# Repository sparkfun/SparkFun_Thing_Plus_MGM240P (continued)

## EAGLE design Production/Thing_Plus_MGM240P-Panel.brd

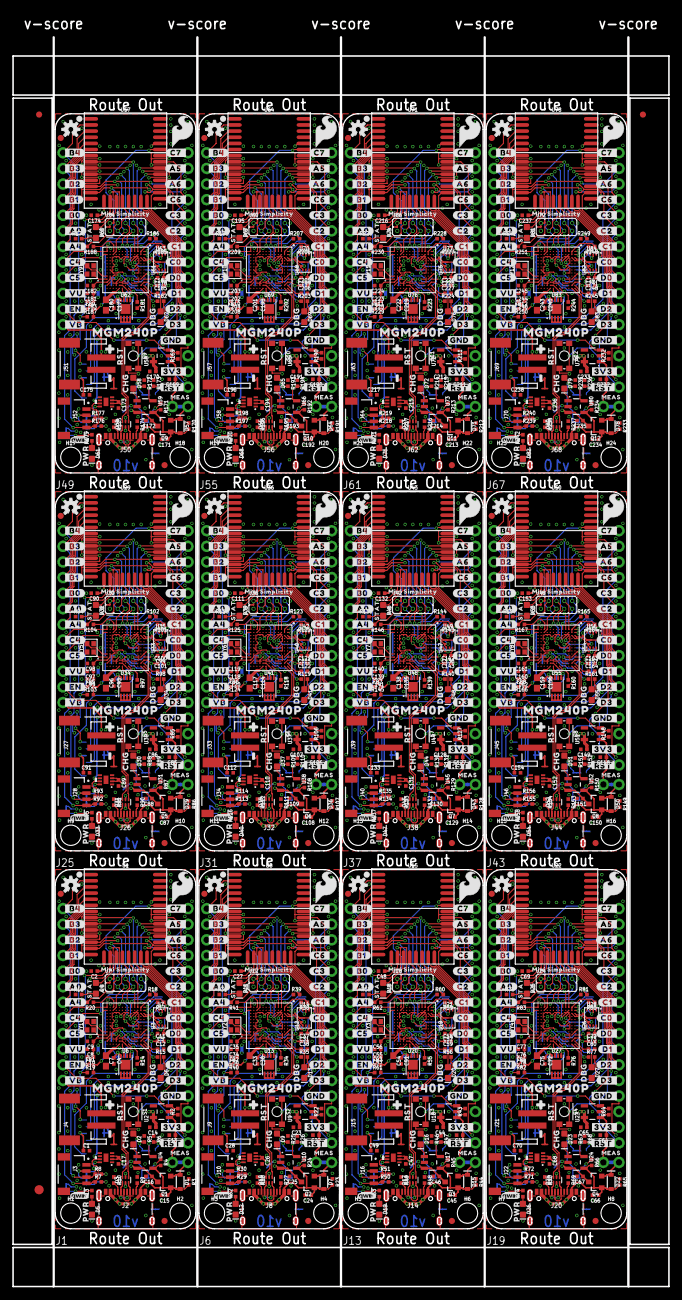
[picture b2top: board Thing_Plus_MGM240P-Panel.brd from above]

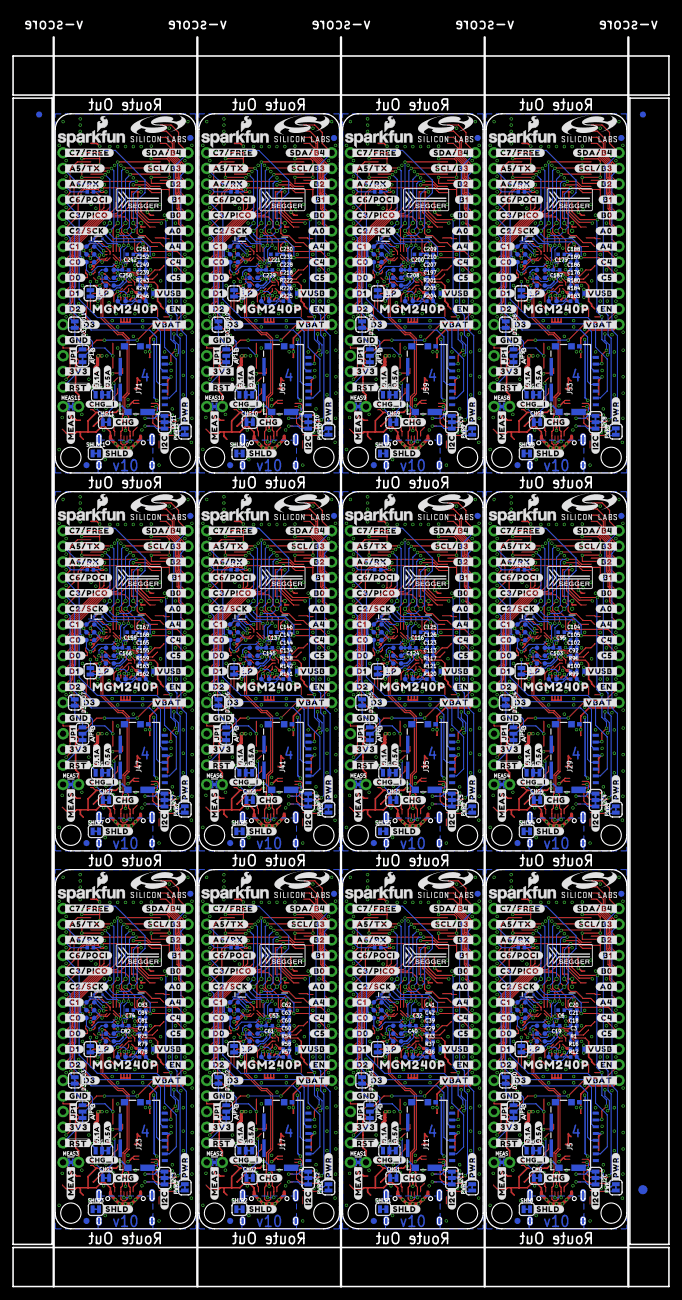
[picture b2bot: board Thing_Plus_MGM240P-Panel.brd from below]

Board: 4 copper layers, 106.7 x 203.2 mm, 2178 parts (963 on the bottom side), 948 nets.

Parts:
C1, C6, C28, C32, C49, C53, C70, C74, C91, C95, C112, C116, C133, C137, C154, C158, C175, C179, C196, C200, C217, C221, C238, C242: 10uF; 0402-TIGHT
C2, C3, C4, C5, C17, C18, C19, C20, C21, C26, C27, C29, C30, C31, C39, C40, C41, C42, C47, C48, C50, C51, C52, C60, C61, C62, C63, C68, C69, C71, C72, C73, C81, C82, C83, C84, C89, C90, C92, C93, C94, C102, C103, C104, C105, C110, C111, C113, C114, C115, C123, C124, C125, C126, C131, C132, C134, C135, C136, C144, C145, C146, C147, C152, C153, C155, C156, C157, C165, C166, C167, C168, C173, C174, C176, C177, C178, C186, C187, C188, C189, C194, C195, C197, C198, C199, C207, C208, C209, C210, C215, C216, C218, C219, C220, C228, C229, C230, C231, C236, C237, C239, C240, C241, C249, C250, C251, C252: 0.1uF; 0402-TIGHT
C7, C33, C54, C75, C96, C117, C138, C159, C180, C201, C222, C243: 1.0uF; 0603
C8, C9, C34, C35, C55, C56, C76, C77, C97, C98, C118, C119, C139, C140, C160, C161, C181, C182, C202, C203, C223, C224, C244, C245: 10nF; 0402-TIGHT
C10, C11, C13, C22, C36, C37, C43, C57, C58, C64, C78, C79, C85, C99, C100, C106, C120, C121, C127, C141, C142, C148, C162, C163, C169, C183, C184, C190, C204, C205, C211, C225, C226, C232, C246, C247: 1.0uF; 0402-TIGHT
C12, C15, C16, C24, C25, C38, C45, C46, C59, C66, C67, C80, C87, C88, C101, C108, C109, C122, C129, C130, C143, C150, C151, C164, C171, C172, C185, C192, C193, C206, C213, C214, C227, C234, C235, C248: 4.7uF; 0402-TIGHT
C14, C23, C44, C65, C86, C107, C128, C149, C170, C191, C212, C233: 2.2uF; 0402-TIGHT
CHG, CHG1, CHG2, CHG3, CHG4, CHG5, CHG6, CHG7, CHG8, CHG9, CHG10, CHG11: JUMPER-SMT_2_NC_TRACE_SILK; SMT-JUMPER_2_NC_TRACE_SILK
CHG_I, CHG_I1, CHG_I2, CHG_I3, CHG_I4, CHG_I5, CHG_I6, CHG_I7, CHG_I8, CHG_I9, CHG_I10, CHG_I11: JUMPER-SMT_3_1-NC_TRACE_SILK; SMT-JUMPER_3_1-NC_TRACE_SILK
D1, D7, D15, D22, D29, D36, D43, D50, D57, D64, D71, D78: 1A/23V/620mV; SOD-323
D2, D9, D16, D23, D30, D37, D44, D51, D58, D65, D72, D79: Yellow; LED-0603
D3, D10, D17, D24, D31, D38, D45, D52, D59, D66, D73, D80: PRTR5V0U2F; SOT886
D3_ISO, D3_ISO1, D3_ISO2, D3_ISO3, D3_ISO4, D3_ISO5, D3_ISO6, D3_ISO7, D3_ISO8, D3_ISO9, D3_ISO10, D3_ISO11: JUMPER-SMT_2_NC_TRACE_SILK; SMT-JUMPER_2_NC_TRACE_SILK
D4, D6, D11, D13, D18, D20, D25, D27, D32, D34, D39, D41, D46, D48, D53, D55, D60, D62, D67, D69, D74, D76, D81, D83: BLUE; LED-0603
D5, D12, D19, D26, D33, D40, D47, D54, D61, D68, D75, D82: RED; LED-0603
D8, D14, D21, D28, D35, D42, D49, D56, D63, D70, D77, D84: 120mA/40V/370mV; SOD-523
E$1, E$2, E$3, E$4: FIDUCIAL-1X2
E$5, E$6: FIDUCIAL-1.5X3
FB1, FB2, FB3, FB4, FB5, FB6, FB7, FB8, FB9, FB10, FB11, FB12: FERRITE_BEAD-120_OHM-0402T; 0402-TIGHT
FD1, FD2, FD3, FD4, FD5, FD6, FD7, FD8, FD9, FD10, FD11, FD12, FD13, FD14, FD15, FD16, FD17, FD18, FD19, FD20, FD21, FD22, FD23, FD24, FD25, FD26, FD27, FD28, FD29, FD30, FD31, FD32, FD33, FD34, FD35, FD36, FD37, FD38, FD39, FD40, FD41, FD42, FD43, FD44, FD45, FD46, FD47, FD48: FIDUCIAL1X2; FIDUCIAL-1X2
H1, H2, H3, H4, H5, H6, H7, H8, H9, H10, H11, H12, H13, H14, H15, H16, H17, H18, H19, H20, H21, H22, H23, H24: STAND-OFF
I2C, I2C1, I2C2, I2C3, I2C4, I2C5, I2C6, I2C7, I2C8, I2C9, I2C10, I2C11: JUMPER-SMT_3_2-NC_TRACE_SILK; SMT-JUMPER_3_2-NC_TRACE_SILK
J1, J6, J13, J19, J25, J31, J37, J43, J49, J55, J61, J67: THING_PLUS_LOGICAL; THING_PLUS
J2, J8, J14, J20, J26, J32, J38, J44, J50, J56, J62, J68: USB Female Type C Connector; USB-C-16P-4LAYER-ISOLATED
J3, J10, J16, J22, J28, J34, J40, J46, J52, J58, J64, J70: QWIIC_RIGHT_ANGLE; JST04_1MM_RA
J4, J9, J15, J21, J27, J33, J39, J45, J51, J57, J63, J69: JST-2-SMD
J5, J11, J17, J23, J29, J35, J41, J47, J53, J59, J65, J71: MICRO-SDFRICTION; MICROSD_TINY
J7, J12, J18, J24, J30, J36, J42, J48, J54, J60, J66, J72: 2X5_PTH_SILK_.05
JP1, JP2, JP3, JP4, JP5, JP6, JP7, JP8, JP9, JP10, JP11, JP12: JUMPER-SMT_3_1-NC_TRACE_SILK; SMT-JUMPER_3_1-NC_TRACE_SILK
LOGO1, LOGO4, LOGO7, LOGO10, LOGO13, LOGO16, LOGO19, LOGO22, LOGO25, LOGO28, LOGO31, LOGO34: SFE_LOGO_NAME_FLAME.1_INCH; SFE_LOGO_NAME_FLAME_.1
LOGO2, LOGO5, LOGO8, LOGO11, LOGO14, LOGO17, LOGO20, LOGO23, LOGO26, LOGO29, LOGO32, LOGO35: QWIIC_LOGO_3MM; QWIIC_3MM
LOGO3, LOGO6, LOGO9, LOGO12, LOGO15, LOGO18, LOGO21, LOGO24, LOGO27, LOGO30, LOGO33, LOGO36: OSHW-LOGOS; OSHW-LOGO-S
LP, LP1, LP2, LP3, LP4, LP5, LP6, LP7, LP8, LP9, LP10, LP11: JUMPER-SMT_2_NC_TRACE_SILK; SMT-JUMPER_2_NC_TRACE_SILK
MEAS, MEAS1, MEAS2, MEAS3, MEAS4, MEAS5, MEAS6, MEAS7, MEAS8, MEAS9, MEAS10, MEAS11: JUMPER-COMBO_2_NC_TRACE; COMBO-JUMPER_2_NC_TRACE
PWR, PWR1, PWR2, PWR3, PWR4, PWR5, PWR6, PWR7, PWR8, PWR9, PWR10, PWR11: JUMPER-SMT_2_NC_TRACE_SILK; SMT-JUMPER_2_NC_TRACE_SILK
Q1, Q2, Q3, Q4, Q5, Q6, Q7, Q8, Q9, Q10, Q11, Q12: 20V/4.2A/52mΩ/1.4W; SOT23-3
R1, R13, R18, R32, R33, R39, R53, R54, R60, R74, R75, R81, R95, R96, R102, R116, R117, R123, R137, R138, R144, R158, R159, R165, R179, R180, R186, R200, R201, R207, R221, R222, R228, R242, R243, R249: 1k; 0402-TIGHT
R2, R3, R6, R17, R22, R23, R26, R38, R43, R44, R47, R59, R64, R65, R68, R80, R85, R86, R89, R101, R106, R107, R110, R122, R127, R128, R131, R143, R148, R149, R152, R164, R169, R170, R173, R185, R190, R191, R194, R206, R211, R212, R215, R227, R232, R233, R236, R248: 10k; 0402-TIGHT
R4, R24, R45, R66, R87, R108, R129, R150, R171, R192, R213, R234: 4.7k; 0402-TIGHT
R5, R25, R46, R67, R88, R109, R130, R151, R172, R193, R214, R235: 2.0K; 0402-TIGHT
R7, R8, R11, R12, R15, R16, R29, R30, R31, R35, R36, R37, R50, R51, R52, R56, R57, R58, R71, R72, R73, R77, R78, R79, R92, R93, R94, R98, R99, R100, R113, R114, R115, R119, R120, R121, R134, R135, R136, R140, R141, R142, R155, R156, R157, R161, R162, R163, R176, R177, R178, R182, R183, R184, R197, R198, R199, R203, R204, R205, R218, R219, R220, R224, R225, R226, R239, R240, R241, R245, R246, R247: 2.2k; 0402-TIGHT
R9, R10, R27, R28, R48, R49, R69, R70, R90, R91, R111, R112, R132, R133, R153, R154, R174, R175, R195, R196, R216, R217, R237, R238: 5.1k; 0402-TIGHT
R14, R19, R34, R40, R55, R61, R76, R82, R97, R103, R118, R124, R139, R145, R160, R166, R181, R187, R202, R208, R223, R229, R244, R250: 100k; 0402-TIGHT
R20, R21, R41, R42, R62, R63, R83, R84, R104, R105, R125, R126, R146, R147, R167, R168, R188, R189, R209, R210, R230, R231, R251, R252: 330; 0402-TIGHT
S1, S2, S3, S4, S5, S6, S7, S8, S9, S10, S11, S12: MOMENTARY-SWITCH-SPST-SMD-4.6X2.8MM; TACTILE_SWITCH_SMD_4.6X2.8MM
SHLD, SHLD1, SHLD2, SHLD3, SHLD4, SHLD5, SHLD6, SHLD7, SHLD8, SHLD9, SHLD10, SHLD11: JUMPER-SMT_2_NC_TRACE_SILK; SMT-JUMPER_2_NC_TRACE_SILK
TP1, TP2, TP3, TP4, TP5, TP6, TP7, TP8, TP9, TP10, TP11, TP12, TP13, TP14, TP15, TP16, TP17, TP18, TP19, TP20, TP21, TP22, TP23, TP24, TP25, TP26, TP27, TP28, TP29, TP30, TP31, TP32, TP33, TP34, TP35, TP36, TP37, TP38, TP39, TP40, TP41, TP42, TP43, TP44, TP45, TP46, TP47, TP48, TP49, TP50, TP51, TP52, TP53, TP54, TP55, TP56, TP57, TP58, TP59, TP60, TP61, TP62, TP63, TP64, TP65, TP66, TP67, TP68, TP69, TP70, TP71, TP72, TP73, TP74, TP75, TP76, TP77, TP78, TP79, TP80, TP81, TP82, TP83, TP84, TP85, TP86, TP87, TP88, TP89, TP90, TP91, TP92, TP93, TP94, TP95, TP96, TP97, TP98, TP99, TP100, TP101, TP102, TP103, TP104, TP105, TP106, TP107, TP108, TP109, TP110, TP111, TP112, TP113, TP114, TP115, TP116, TP117, TP118, TP119, TP120, TP121, TP122, TP123, TP124, TP125, TP126, TP127, TP128, TP129, TP130, TP131, TP132, TP133, TP134, TP135, TP136, TP137, TP138, TP139, TP140, TP141, TP142, TP143, TP144, TP145, TP146, TP147, TP148, TP149, TP150, TP151, TP152, TP153, TP154, TP155, TP156, TP157, TP158, TP159, TP160, TP161, TP162, TP163, TP164, TP165, TP166, TP167, TP168: TEST-POINT3; PAD.03X.03
U1, U8, U15, U22, U29, U36, U43, U50, U57, U64, U71, U78: MGM240P
U2, U9, U16, U23, U30, U37, U44, U51, U58, U65, U72, U79: XC6222B331MR-G; SOT23-5
U3, U12, U19, U26, U33, U40, U47, U54, U61, U68, U75, U82: EFM32GG12B410F1024GL120
U4, U10, U17, U24, U31, U38, U45, U52, U59, U66, U73, U80: MCP73831; SOT23-5
U5, U11, U18, U25, U32, U39, U46, U53, U60, U67, U74, U81: MAX17048; DFN-8
U6, U13, U20, U27, U34, U41, U48, U55, U62, U69, U76, U83: M24C02-FMC6TG
U7, U14, U21, U28, U35, U42, U49, U56, U63, U70, U77, U84: MX25R8035FZUIL0
U$1, U$110, U$193, U$276, U$359, U$442, U$525, U$608, U$691, U$774, U$857, U$940: #_B4#0
U$2, U$111, U$194, U$277, U$360, U$443, U$526, U$609, U$692, U$775, U$858, U$941: #_B3#0
U$3, U$112, U$195, U$278, U$361, U$444, U$527, U$610, U$693, U$776, U$859, U$942: #_B2#0
U$4, U$113, U$196, U$279, U$362, U$445, U$528, U$611, U$694, U$777, U$860, U$943: #_B1#0
U$5, U$84, U$167, U$250, U$333, U$416, U$499, U$582, U$665, U$748, U$831, U$914: #SHLD#0
U$6, U$114, U$197, U$280, U$363, U$446, U$529, U$612, U$695, U$778, U$861, U$944: #_B0#0
U$7, U$115, U$198, U$281, U$364, U$447, U$530, U$613, U$696, U$779, U$862, U$945: #_A0#0
U$8, U$158, U$241, U$324, U$407, U$490, U$573, U$656, U$739, U$822, U$905, U$988: #_A4#0
U$9, U$116, U$199, U$282, U$365, U$448, U$531, U$614, U$697, U$780, U$863, U$946: #_C5#0
U$10, U$117, U$200, U$283, U$366, U$449, U$532, U$615, U$698, U$781, U$864, U$947: #_C4#0
U$11, U$118, U$201, U$284, U$367, U$450, U$533, U$616, U$699, U$782, U$865, U$948: #C7_#0
U$12, U$119, U$202, U$285, U$368, U$451, U$534, U$617, U$700, U$783, U$866, U$949: #A5_#0
U$13, U$120, U$203, U$286, U$369, U$452, U$535, U$618, U$701, U$784, U$867, U$950: #A6_#0
U$14, U$121, U$204, U$287, U$370, U$453, U$536, U$619, U$702, U$785, U$868, U$951: #C6_#0
U$15, U$122, U$205, U$288, U$371, U$454, U$537, U$620, U$703, U$786, U$869, U$952: #C3_#0
U$16, U$123, U$206, U$289, U$372, U$455, U$538, U$621, U$704, U$787, U$870, U$953: #C2_#0
U$17, U$124, U$207, U$290, U$373, U$456, U$539, U$622, U$705, U$788, U$871, U$954: #C1_#0
U$18, U$125, U$208, U$291, U$374, U$457, U$540, U$623, U$706, U$789, U$872, U$955: #C0_#0
U$19, U$105, U$188, U$271, U$354, U$437, U$520, U$603, U$686, U$769, U$852, U$935: #PWR#0
U$20, U$106, U$189, U$272, U$355, U$438, U$521, U$604, U$687, U$770, U$853, U$936: PWR0
U$21, U$85, U$168, U$251, U$334, U$417, U$500, U$583, U$666, U$749, U$832, U$915: #GND_#0
U$22, U$86, U$169, U$252, U$335, U$418, U$501, U$584, U$667, U$750, U$833, U$916: #3V3_#0
U$23, U$58, U$91, U$101, U$174, U$184, U$257, U$267, U$340, U$350, U$423, U$433, U$506, U$516, U$589, U$599, U$672, U$682, U$755, U$765, U$838, U$848, U$921, U$931: MGM240P0
U$24, U$126, U$209, U$292, U$375, U$458, U$541, U$624, U$707, U$790, U$873, U$956: #D0_#0
U$25, U$87, U$170, U$253, U$336, U$419, U$502, U$585, U$668, U$751, U$834, U$917: #_VB#0
U$26, U$88, U$171, U$254, U$337, U$420, U$503, U$586, U$669, U$752, U$835, U$918: #_VU#0
U$27, U$89, U$172, U$255, U$338, U$421, U$504, U$587, U$670, U$753, U$836, U$919: #_EN#0
U$28, U$90, U$173, U$256, U$339, U$422, U$505, U$588, U$671, U$754, U$837, U$920: ##RST##0
U$29, U$92, U$175, U$258, U$341, U$424, U$507, U$590, U$673, U$756, U$839, U$922: SFE_LOGO_FLAME_.2
U$30, U$93, U$176, U$259, U$342, U$425, U$508, U$591, U$674, U$757, U$840, U$923: #0
U$31, U$94, U$177, U$260, U$343, U$426, U$509, U$592, U$675, U$758, U$841, U$924: #1
U$32, U$127, U$210, U$293, U$376, U$459, U$542, U$625, U$708, U$791, U$874, U$957: #D1_#0
U$33, U$157, U$240, U$323, U$406, U$489, U$572, U$655, U$738, U$821, U$904, U$987: #LP#0
U$34, U$142, U$225, U$308, U$391, U$474, U$557, U$640, U$723, U$806, U$889, U$972: #_A6#RX#0
U$35, U$143, U$226, U$309, U$392, U$475, U$558, U$641, U$724, U$807, U$890, U$973: #_C6#POCI#0
U$36, U$144, U$227, U$310, U$393, U$476, U$559, U$642, U$725, U$808, U$891, U$974: #_C3#PICO#0
U$37, U$145, U$228, U$311, U$394, U$477, U$560, U$643, U$726, U$809, U$892, U$975: #_C2#SCK#0
U$38, U$146, U$229, U$312, U$395, U$478, U$561, U$644, U$727, U$810, U$893, U$976: MINI_SIMPLICITY0
U$39, U$128, U$211, U$294, U$377, U$460, U$543, U$626, U$709, U$792, U$875, U$958: #_C1#0
U$40, U$129, U$212, U$295, U$378, U$461, U$544, U$627, U$710, U$793, U$876, U$959: #_C0#0
U$41, U$130, U$213, U$296, U$379, U$462, U$545, U$628, U$711, U$794, U$877, U$960: #_D0#0
U$42, U$131, U$214, U$297, U$380, U$463, U$546, U$629, U$712, U$795, U$878, U$961: #_D1#0
U$43, U$95, U$178, U$261, U$344, U$427, U$510, U$593, U$676, U$759, U$842, U$925: #_GND#0
U$44, U$96, U$179, U$262, U$345, U$428, U$511, U$594, U$677, U$760, U$843, U$926: #_3V3#0
U$45, U$97, U$180, U$263, U$346, U$429, U$512, U$595, U$678, U$761, U$844, U$927: #_#RST##0
U$46, U$132, U$215, U$298, U$381, U$464, U$547, U$630, U$713, U$796, U$879, U$962: #_D2#0
U$47, U$162, U$245, U$328, U$411, U$494, U$577, U$660, U$743, U$826, U$909, U$992: SILICON_LABS_LOGO
U$48, U$133, U$216, U$299, U$382, U$465, U$548, U$631, U$714, U$797, U$880, U$963: #C4_#0
U$49, U$134, U$217, U$300, U$383, U$466, U$549, U$632, U$715, U$798, U$881, U$964: #C5_#0
U$50, U$159, U$242, U$325, U$408, U$491, U$574, U$657, U$740, U$823, U$906, U$989: #A4_#0
U$51, U$135, U$218, U$301, U$384, U$467, U$550, U$633, U$716, U$799, U$882, U$965: #A0_#0
U$52, U$136, U$219, U$302, U$385, U$468, U$551, U$634, U$717, U$800, U$883, U$966: #B0_#0
U$53, U$137, U$220, U$303, U$386, U$469, U$552, U$635, U$718, U$801, U$884, U$967: #B2_#0
U$54, U$138, U$221, U$304, U$387, U$470, U$553, U$636, U$719, U$802, U$885, U$968: #B1_#0
U$55, U$98, U$181, U$264, U$347, U$430, U$513, U$596, U$679, U$762, U$845, U$928: #VBAT_#0
U$56, U$99, U$182, U$265, U$348, U$431, U$514, U$597, U$680, U$763, U$846, U$929: #VUSB_#0
U$57, U$100, U$183, U$266, U$349, U$432, U$515, U$598, U$681, U$764, U$847, U$930: #EN_#0
U$59, U$102, U$185, U$268, U$351, U$434, U$517, U$600, U$683, U$766, U$849, U$932: #MEAS#0
U$60, U$103, U$186, U$269, U$352, U$435, U$518, U$601, U$684, U$767, U$850, U$933: #CHG#0
U$61, U$104, U$187, U$270, U$353, U$436, U$519, U$602, U$685, U$768, U$851, U$934: #I2C#0
U$62, U$153, U$236, U$319, U$402, U$485, U$568, U$651, U$734, U$817, U$900, U$983: #D2_#0
U$63, U$151, U$234, U$317, U$400, U$483, U$566, U$649, U$732, U$815, U$898, U$981: #0#5A#0
U$64, U$152, U$235, U$318, U$401, U$484, U$567, U$650, U$733, U$816, U$899, U$982: #0#1A#0
U$65, U$160, U$243, U$326, U$409, U$492, U$575, U$658, U$741, U$824, U$907, U$990: SEGGER_LOGO
U$66, U$148, U$231, U$314, U$397, U$480, U$563, U$646, U$729, U$812, U$895, U$978: MEAS81
U$67, U$107, U$190, U$273, U$356, U$439, U$522, U$605, U$688, U$771, U$854, U$937: CHG0
U$68, U$108, U$191, U$274, U$357, U$440, U$523, U$606, U$689, U$772, U$855, U$938: STAT0
U$69, U$164, U$247, U$330, U$413, U$496, U$579, U$662, U$745, U$828, U$911, U$994: #JP1#0
U$70, U$109, U$192, U$275, U$358, U$441, U$524, U$607, U$690, U$773, U$856, U$939: RST0
U$71, U$141, U$224, U$307, U$390, U$473, U$556, U$639, U$722, U$805, U$888, U$971: #_A5#TX#0
U$72, U$147, U$230, U$313, U$396, U$479, U$562, U$645, U$728, U$811, U$894, U$977: A80
U$73, U$139, U$222, U$305, U$388, U$471, U$554, U$637, U$720, U$803, U$886, U$969: #SDA#B4_#0
U$74, U$140, U$223, U$306, U$389, U$472, U$555, U$638, U$721, U$804, U$887, U$970: #SCL#B3_#0
U$75, U$149, U$232, U$315, U$398, U$481, U$564, U$647, U$730, U$813, U$896, U$979: ORDERING_INSTRUCTIONS
U$76, U$150, U$233, U$316, U$399, U$482, U$565, U$648, U$731, U$814, U$897, U$980: FOUR_LAYER_WARNING
U$77, U$154, U$237, U$320, U$403, U$486, U$569, U$652, U$735, U$818, U$901, U$984: #D3_#0
U$78, U$155, U$238, U$321, U$404, U$487, U$570, U$653, U$736, U$819, U$902, U$985: DBG0
U$79, U$156, U$239, U$322, U$405, U$488, U$571, U$654, U$737, U$820, U$903, U$986: #_C7#FREE#0
U$80, U$165, U$248, U$331, U$414, U$497, U$580, U$663, U$746, U$829, U$912, U$995: A0
U$81, U$166, U$249, U$332, U$415, U$498, U$581, U$664, U$747, U$830, U$913, U$996: B0
U$82, U$161, U$244, U$327, U$410, U$493, U$576, U$659, U$742, U$825, U$908, U$991: #D3#4
U$83, U$163, U$246, U$329, U$412, U$495, U$578, U$661, U$744, U$827, U$910, U$993: #CHG_I#0
Y1, Y2, Y3, Y4, Y5, Y6, Y7, Y8, Y9, Y10, Y11, Y12: CRYSTAL-48MHZ; CRYSTAL-SMD-2.0X1.6MM-ECS

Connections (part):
3.3V: C1.1, C2.1, C4.1, C5.1, C6.1, C14.1, C18.1, C19.1, C20.1, C21.1, FB1.2, I2C.2, J1.27, J3.2, J5.4, J7.1, PWR.2, R1.2, R12.2, R14.2, R16.2, R17.2, R19.2, TP1.1, U1.15, U2.5, U3.C6, U3.C9, U3.G3, U3.H11, U3.J11, U3.K3, U3.L4, U3.L7, U6.8, U7.3, U7.8
3.3V1: C23.1, C27.1, C28.1, C30.1, C31.1, C32.1, C39.1, C40.1, C41.1, C42.1, FB2.2, I2C1.2, J6.27, J10.2, J11.4, J12.1, PWR1.2, R33.2, R34.2, R36.2, R37.2, R38.2, R40.2, TP15.1, U8.15, U9.5, U12.C6, U12.C9, U12.G3, U12.H11, U12.J11, U12.K3, U12.L4, U12.L7, U13.8, U14.3, U14.8
3.3V2: C44.1, C48.1, C49.1, C51.1, C52.1, C53.1, C60.1, C61.1, C62.1, C63.1, FB3.2, I2C2.2, J13.27, J16.2, J17.4, J18.1, PWR2.2, R54.2, R55.2, R57.2, R58.2, R59.2, R61.2, TP29.1, U15.15, U16.5, U19.C6, U19.C9, U19.G3, U19.H11, U19.J11, U19.K3, U19.L4, U19.L7, U20.8, U21.3, U21.8
3.3V3: C65.1, C69.1, C70.1, C72.1, C73.1, C74.1, C81.1, C82.1, C83.1, C84.1, FB4.2, I2C3.2, J19.27, J22.2, J23.4, J24.1, PWR3.2, R75.2, R76.2, R78.2, R79.2, R80.2, R82.2, TP43.1, U22.15, U23.5, U26.C6, U26.C9, U26.G3, U26.H11, U26.J11, U26.K3, U26.L4, U26.L7, U27.8, U28.3, U28.8
3.3V4: C86.1, C90.1, C91.1, C93.1, C94.1, C95.1, C102.1, C103.1, C104.1, C105.1, FB5.2, I2C4.2, J25.27, J28.2, J29.4, J30.1, PWR4.2, R96.2, R97.2, R99.2, R100.2, R101.2, R103.2, TP57.1, U29.15, U30.5, U33.C6, U33.C9, U33.G3, U33.H11, U33.J11, U33.K3, U33.L4, U33.L7, U34.8, U35.3, U35.8
3.3V5: C107.1, C111.1, C112.1, C114.1, C115.1, C116.1, C123.1, C124.1, C125.1, C126.1, FB6.2, I2C5.2, J31.27, J34.2, J35.4, J36.1, PWR5.2, R117.2, R118.2, R120.2, R121.2, R122.2, R124.2, TP71.1, U36.15, U37.5, U40.C6, U40.C9, U40.G3, U40.H11, U40.J11, U40.K3, U40.L4, U40.L7, U41.8, U42.3, U42.8
3.3V6: C128.1, C132.1, C133.1, C135.1, C136.1, C137.1, C144.1, C145.1, C146.1, C147.1, FB7.2, I2C6.2, J37.27, J40.2, J41.4, J42.1, PWR6.2, R138.2, R139.2, R141.2, R142.2, R143.2, R145.2, TP85.1, U43.15, U44.5, U47.C6, U47.C9, U47.G3, U47.H11, U47.J11, U47.K3, U47.L4, U47.L7, U48.8, U49.3, U49.8
3.3V7: C149.1, C153.1, C154.1, C156.1, C157.1, C158.1, C165.1, C166.1, C167.1, C168.1, FB8.2, I2C7.2, J43.27, J46.2, J47.4, J48.1, PWR7.2, R159.2, R160.2, R162.2, R163.2, R164.2, R166.2, TP99.1, U50.15, U51.5, U54.C6, U54.C9, U54.G3, U54.H11, U54.J11, U54.K3, U54.L4, U54.L7, U55.8, U56.3, U56.8
3.3V8: C170.1, C174.1, C175.1, C177.1, C178.1, C179.1, C186.1, C187.1, C188.1, C189.1, FB9.2, I2C8.2, J49.27, J52.2, J53.4, J54.1, PWR8.2, R180.2, R181.2, R183.2, R184.2, R185.2, R187.2, TP113.1, U57.15, U58.5, U61.C6, U61.C9, U61.G3, U61.H11, U61.J11, U61.K3, U61.L4, U61.L7, U62.8, U63.3, U63.8
3.3V9: C191.1, C195.1, C196.1, C198.1, C199.1, C200.1, C207.1, C208.1, C209.1, C210.1, FB10.2, I2C9.2, J55.27, J58.2, J59.4, J60.1, PWR9.2, R201.2, R202.2, R204.2, R205.2, R206.2, R208.2, TP127.1, U64.15, U65.5, U68.C6, U68.C9, U68.G3, U68.H11, U68.J11, U68.K3, U68.L4, U68.L7, U69.8, U70.3, U70.8
3.3V10: C212.1, C216.1, C217.1, C219.1, C220.1, C221.1, C228.1, C229.1, C230.1, C231.1, FB11.2, I2C10.2, J61.27, J64.2, J65.4, J66.1, PWR10.2, R222.2, R223.2, R225.2, R226.2, R227.2, R229.2, TP141.1, U71.15, U72.5, U75.C6, U75.C9, U75.G3, U75.H11, U75.J11, U75.K3, U75.L4, U75.L7, U76.8, U77.3, U77.8
3.3V11: C233.1, C237.1, C238.1, C240.1, C241.1, C242.1, C249.1, C250.1, C251.1, C252.1, FB12.2, I2C11.2, J67.27, J70.2, J71.4, J72.1, PWR11.2, R243.2, R244.2, R246.2, R247.2, R248.2, R250.2, TP155.1, U78.15, U79.5, U82.C6, U82.C9, U82.G3, U82.H11, U82.J11, U82.K3, U82.L4, U82.L7, U83.8, U84.3, U84.8
!DBG_RESET!: TP3.1, U3.L8, U3.M7
!DBG_RESET!1: TP17.1, U12.L8, U12.M7
!DBG_RESET!2: TP31.1, U19.L8, U19.M7
!DBG_RESET!3: TP45.1, U26.L8, U26.M7
!DBG_RESET!4: TP59.1, U33.L8, U33.M7
!DBG_RESET!5: TP73.1, U40.L8, U40.M7
!DBG_RESET!6: TP87.1, U47.L8, U47.M7
!DBG_RESET!7: TP101.1, U54.L8, U54.M7
!DBG_RESET!8: TP115.1, U61.L8, U61.M7
!DBG_RESET!9: TP129.1, U68.L8, U68.M7
!DBG_RESET!10: TP143.1, U75.L8, U75.M7
!DBG_RESET!11: TP157.1, U82.L8, U82.M7
!RESET!: J7.3, JP1.2, S1.3, S1.4, U1.31, U3.D1
!RESET!1: J12.3, JP2.2, S2.3, S2.4, U8.31, U12.D1
!RESET!2: J18.3, JP3.2, S3.3, S3.4, U15.31, U19.D1
!RESET!3: J24.3, JP4.2, S4.3, S4.4, U22.31, U26.D1
!RESET!4: J30.3, JP5.2, S5.3, S5.4, U29.31, U33.D1
!RESET!5: J36.3, JP6.2, S6.3, S6.4, U36.31, U40.D1
!RESET!6: J42.3, JP7.2, S7.3, S7.4, U43.31, U47.D1
!RESET!7: J48.3, JP8.2, S8.3, S8.4, U50.31, U54.D1
!RESET!8: J54.3, JP9.2, S9.3, S9.4, U57.31, U61.D1
!RESET!9: J60.3, JP10.2, S10.3, S10.4, U64.31, U68.D1
!RESET!10: J66.3, JP11.2, S11.3, S11.4, U71.31, U75.D1
!RESET!11: J72.3, JP12.2, S12.3, S12.4, U78.31, U82.D1
!SD_CS!/PA01: J11.2, R40.1, U8.16
!SD_CS!/PA02: J17.2, R61.1, U15.16
!SD_CS!/PA03: J23.2, R82.1, U22.16
!SD_CS!/PA04: J29.2, R103.1, U29.16
!SD_CS!/PA05: J35.2, R124.1, U36.16
!SD_CS!/PA06: J41.2, R145.1, U43.16
!SD_CS!/PA07: J5.2, R19.1, U1.16
!SD_CS!/PA08: J47.2, R166.1, U50.16
!SD_CS!/PA09: J53.2, R187.1, U57.16
!SD_CS!/PA10: J59.2, R208.1, U64.16
!SD_CS!/PA11: J65.2, R229.1, U71.16
!SD_CS!/PA12: J71.2, R250.1, U78.16
A0: D3_ISO.2, J1.24, JP1.1
A1: D3_ISO1.2, J6.24, JP2.1
A2: D3_ISO2.2, J13.24, JP3.1
A3: D3_ISO3.2, J19.24, JP4.1
A4: D3_ISO4.2, J25.24, JP5.1
A5: D3_ISO5.2, J31.24, JP6.1
A6: D3_ISO6.2, J37.24, JP7.1
A7: D3_ISO7.2, J43.24, JP8.1
A8: D3_ISO8.2, J49.24, JP9.1
A9: D3_ISO9.2, J55.24, JP10.1
A10: D3_ISO10.2, J61.24, JP11.1
A11: D3_ISO11.2, J67.24, JP12.1
DBG_CS: R17.1, TP10.1, U3.B1, U3.B2, U7.1
DBG_CS1: R38.1, TP24.1, U12.B1, U12.B2, U14.1
DBG_CS2: R59.1, TP38.1, U19.B1, U19.B2, U21.1
DBG_CS3: R80.1, TP52.1, U26.B1, U26.B2, U28.1
DBG_CS4: R101.1, TP66.1, U33.B1, U33.B2, U35.1
DBG_CS5: R122.1, TP80.1, U40.B1, U40.B2, U42.1
DBG_CS6: R143.1, TP94.1, U47.B1, U47.B2, U49.1
DBG_CS7: R164.1, TP108.1, U54.B1, U54.B2, U56.1
DBG_CS8: R185.1, TP122.1, U61.B1, U61.B2, U63.1
DBG_CS9: R206.1, TP136.1, U68.B1, U68.B2, U70.1
DBG_CS10: R227.1, TP150.1, U75.B1, U75.B2, U77.1
DBG_CS11: R248.1, TP164.1, U82.B1, U82.B2, U84.1
DBG_LED_PWR: C12.1, D6.A, U3.A12
DBG_LED_PWR1: C38.1, D13.A, U12.A12
DBG_LED_PWR2: C59.1, D20.A, U19.A12
DBG_LED_PWR3: C80.1, D27.A, U26.A12
DBG_LED_PWR4: C101.1, D34.A, U33.A12
DBG_LED_PWR5: C122.1, D41.A, U40.A12
DBG_LED_PWR6: C143.1, D48.A, U47.A12
DBG_LED_PWR7: C164.1, D55.A, U54.A12
DBG_LED_PWR8: C185.1, D62.A, U61.A12
DBG_LED_PWR9: C206.1, D69.A, U68.A12
DBG_LED_PWR10: C227.1, D76.A, U75.A12
DBG_LED_PWR11: C248.1, D83.A, U82.A12
DBG_PICO: TP7.1, U3.C3, U7.5
DBG_PICO1: TP21.1, U12.C3, U14.5
DBG_PICO2: TP35.1, U19.C3, U21.5
DBG_PICO3: TP49.1, U26.C3, U28.5
DBG_PICO4: TP63.1, U33.C3, U35.5
DBG_PICO5: TP77.1, U40.C3, U42.5
DBG_PICO6: TP91.1, U47.C3, U49.5
DBG_PICO7: TP105.1, U54.C3, U56.5
DBG_PICO8: TP119.1, U61.C3, U63.5
DBG_PICO9: TP133.1, U68.C3, U70.5
DBG_PICO10: TP147.1, U75.C3, U77.5
DBG_PICO11: TP161.1, U82.C3, U84.5
DBG_POCI: TP8.1, U3.A4, U3.B3, U7.2
DBG_POCI1: TP22.1, U12.A4, U12.B3, U14.2
DBG_POCI2: TP36.1, U19.A4, U19.B3, U21.2
DBG_POCI3: TP50.1, U26.A4, U26.B3, U28.2
DBG_POCI4: TP64.1, U33.A4, U33.B3, U35.2
DBG_POCI5: TP78.1, U40.A4, U40.B3, U42.2
DBG_POCI6: TP92.1, U47.A4, U47.B3, U49.2
DBG_POCI7: TP106.1, U54.A4, U54.B3, U56.2
DBG_POCI8: TP120.1, U61.A4, U61.B3, U63.2
DBG_POCI9: TP134.1, U68.A4, U68.B3, U70.2
DBG_POCI10: TP148.1, U75.A4, U75.B3, U77.2
DBG_POCI11: TP162.1, U82.A4, U82.B3, U84.2
DBG_RX: TP13.1, U3.A1
DBG_RX1: TP27.1, U12.A1
DBG_RX2: TP41.1, U19.A1
DBG_RX3: TP55.1, U26.A1
DBG_RX4: TP69.1, U33.A1
DBG_RX5: TP83.1, U40.A1
DBG_RX6: TP97.1, U47.A1
DBG_RX7: TP111.1, U54.A1
DBG_RX8: TP125.1, U61.A1
DBG_RX9: TP139.1, U68.A1
DBG_RX10: TP153.1, U75.A1
DBG_RX11: TP167.1, U82.A1
DBG_SCK: TP9.1, U3.A3, U7.6
DBG_SCK1: TP23.1, U12.A3, U14.6
DBG_SCK2: TP37.1, U19.A3, U21.6
DBG_SCK3: TP51.1, U26.A3, U28.6
DBG_SCK4: TP65.1, U33.A3, U35.6
DBG_SCK5: TP79.1, U40.A3, U42.6
DBG_SCK6: TP93.1, U47.A3, U49.6
DBG_SCK7: TP107.1, U54.A3, U56.6
DBG_SCK8: TP121.1, U61.A3, U63.6
DBG_SCK9: TP135.1, U68.A3, U70.6
DBG_SCK10: TP149.1, U75.A3, U77.6
DBG_SCK11: TP163.1, U82.A3, U84.6
DBG_SCL: R16.1, TP12.1, U3.H13, U6.6
DBG_SCL1: R37.1, TP26.1, U12.H13, U13.6
DBG_SCL2: R58.1, TP40.1, U19.H13, U20.6
DBG_SCL3: R79.1, TP54.1, U26.H13, U27.6
DBG_SCL4: R100.1, TP68.1, U33.H13, U34.6
DBG_SCL5: R121.1, TP82.1, U40.H13, U41.6
DBG_SCL6: R142.1, TP96.1, U47.H13, U48.6
DBG_SCL7: R163.1, TP110.1, U54.H13, U55.6
DBG_SCL8: R184.1, TP124.1, U61.H13, U62.6
DBG_SCL9: R205.1, TP138.1, U68.H13, U69.6
DBG_SCL10: R226.1, TP152.1, U75.H13, U76.6
DBG_SCL11: R247.1, TP166.1, U82.H13, U83.6
DBG_SDA: R12.1, TP11.1, U3.G13, U3.H12, U3.J12, U6.5
DBG_SDA1: R36.1, TP25.1, U12.G13, U12.H12, U12.J12, U13.5
DBG_SDA2: R57.1, TP39.1, U19.G13, U19.H12, U19.J12, U20.5
DBG_SDA3: R78.1, TP53.1, U26.G13, U26.H12, U26.J12, U27.5
DBG_SDA4: R99.1, TP67.1, U33.G13, U33.H12, U33.J12, U34.5
DBG_SDA5: R120.1, TP81.1, U40.G13, U40.H12, U40.J12, U41.5
DBG_SDA6: R141.1, TP95.1, U47.G13, U47.H12, U47.J12, U48.5
DBG_SDA7: R162.1, TP109.1, U54.G13, U54.H12, U54.J12, U55.5
DBG_SDA8: R183.1, TP123.1, U61.G13, U61.H12, U61.J12, U62.5
DBG_SDA9: R204.1, TP137.1, U68.G13, U68.H12, U68.J12, U69.5
DBG_SDA10: R225.1, TP151.1, U75.G13, U75.H12, U75.J12, U76.5
DBG_SDA11: R246.1, TP165.1, U82.G13, U82.H12, U82.J12, U83.5
DBG_SWCLK: TP4.1, U3.C10
DBG_SWCLK1: TP18.1, U12.C10
DBG_SWCLK2: TP32.1, U19.C10
DBG_SWCLK3: TP46.1, U26.C10
DBG_SWCLK4: TP60.1, U33.C10
DBG_SWCLK5: TP74.1, U40.C10
DBG_SWCLK6: TP88.1, U47.C10
DBG_SWCLK7: TP102.1, U54.C10
DBG_SWCLK8: TP116.1, U61.C10
DBG_SWCLK9: TP130.1, U68.C10
DBG_SWCLK10: TP144.1, U75.C10
DBG_SWCLK11: TP158.1, U82.C10
DBG_SWDIO: TP2.1, U3.A9, U3.B10
DBG_SWDIO1: TP16.1, U12.A9, U12.B10
DBG_SWDIO2: TP30.1, U19.A9, U19.B10
DBG_SWDIO3: TP44.1, U26.A9, U26.B10
DBG_SWDIO4: TP58.1, U33.A9, U33.B10
DBG_SWDIO5: TP72.1, U40.A9, U40.B10
DBG_SWDIO6: TP86.1, U47.A9, U47.B10
DBG_SWDIO7: TP100.1, U54.A9, U54.B10
DBG_SWDIO8: TP114.1, U61.A9, U61.B10
DBG_SWDIO9: TP128.1, U68.A9, U68.B10
DBG_SWDIO10: TP142.1, U75.A9, U75.B10
DBG_SWDIO11: TP156.1, U82.A9, U82.B10
DBG_SWO: TP6.1, U3.A10
DBG_SWO1: TP20.1, U12.A10
DBG_SWO2: TP34.1, U19.A10
DBG_SWO3: TP48.1, U26.A10
DBG_SWO4: TP62.1, U33.A10
DBG_SWO5: TP76.1, U40.A10
DBG_SWO6: TP90.1, U47.A10
DBG_SWO7: TP104.1, U54.A10
DBG_SWO8: TP118.1, U61.A10
DBG_SWO9: TP132.1, U68.A10
DBG_SWO10: TP146.1, U75.A10
DBG_SWO11: TP160.1, U82.A10
DBG_TX: TP14.1, U3.A2
DBG_TX1: TP28.1, U12.A2
DBG_TX2: TP42.1, U19.A2
DBG_TX3: TP56.1, U26.A2
DBG_TX4: TP70.1, U33.A2
DBG_TX5: TP84.1, U40.A2
DBG_TX6: TP98.1, U47.A2
DBG_TX7: TP112.1, U54.A2
DBG_TX8: TP126.1, U61.A2
DBG_TX9: TP140.1, U68.A2
DBG_TX10: TP154.1, U75.A2
DBG_TX11: TP168.1, U82.A2
DBG_WAKE: D8.A, U3.E1
DBG_WAKE1: D14.A, U12.E1
DBG_WAKE2: D21.A, U19.E1
DBG_WAKE3: D28.A, U26.E1
DBG_WAKE4: D35.A, U33.E1
DBG_WAKE5: D42.A, U40.E1
DBG_WAKE6: D49.A, U47.E1
DBG_WAKE7: D56.A, U54.E1
DBG_WAKE8: D63.A, U61.E1
DBG_WAKE9: D70.A, U68.E1
DBG_WAKE10: D77.A, U75.E1
DBG_WAKE11: D84.A, U82.E1
DBG_WP: R14.1, U3.F13, U6.7
DBG_WP1: R34.1, U12.F13, U13.7
DBG_WP2: R55.1, U19.F13, U20.7
DBG_WP3: R76.1, U26.F13, U27.7
DBG_WP4: R97.1, U33.F13, U34.7
DBG_WP5: R118.1, U40.F13, U41.7
DBG_WP6: R139.1, U47.F13, U48.7
DBG_WP7: R160.1, U54.F13, U55.7
DBG_WP8: R181.1, U61.F13, U62.7
DBG_WP9: R202.1, U68.F13, U69.7
DBG_WP10: R223.1, U75.F13, U76.7
DBG_WP11: R244.1, U82.F13, U83.7
EN: J1.11, R2.2, U2.3
EN1: J6.11, R22.2, U9.3
EN2: J13.11, R43.2, U16.3
EN3: J19.11, R64.2, U23.3
EN4: J25.11, R85.2, U30.3
EN5: J31.11, R106.2, U37.3
EN6: J37.11, R127.2, U44.3
EN7: J43.11, R148.2, U51.3
EN8: J49.11, R169.2, U58.3
EN9: J55.11, R190.2, U65.3
EN10: J61.11, R211.2, U72.3
EN11: J67.11, R232.2, U79.3
GND: C1.2, C2.2, C3.2, C4.2, C5.2, C6.2, C7.2, C8.2, C9.2, C10.2, C11.2, C12.2, C13.2, C14.2, C15.2, C16.2, C17.2, C18.2, C19.2, C20.2, C21.2, D3.2, D5.C, J1.25, J2.GND, J2.GND2, J3.1, J4.1, J5.6, J5.GND1, J5.GND2, J5.GND3, J5.GND4, J5.GND5, J5.GND6, J7.2, R3.1, R5.1, R6.1, R9.1, R10.1, R11.1, R18.1, S1.1, S1.2, SHLD.1, TP5.1, U1.1, U1.14, U1.23, U1.32, U1.34, U1.35, U1.36, U2.2, U3.C5, U3.C8, U3.H3, U3.J3, U3.K11, U3.K12, U3.L5, U3.L6, U3.M8, U3.M11, U3.N8, U3.N12, U4.2, U5.1, U5.4, U5.6, U5.9, U6.1, U6.2, U6.3, U6.4, U6.EPAD, U7.4, U7.EPAD, Y1.2, Y1.4
GND1: C22.2, C23.2, C24.2, C25.2, C26.2, C27.2, C28.2, C29.2, C30.2, C31.2, C32.2, C33.2, C34.2, C35.2, C36.2, C37.2, C38.2, C39.2, C40.2, C41.2, C42.2, D10.2, D12.C, J6.25, J8.GND, J8.GND2, J9.1, J10.1, J11.6, J11.GND1, J11.GND2, J11.GND3, J11.GND4, J11.GND5, J11.GND6, J12.2, R23.1, R25.1, R26.1, R27.1, R28.1, R31.1, R39.1, S2.1, S2.2, SHLD1.1, TP19.1, U8.1, U8.14, U8.23, U8.32, U8.34, U8.35, U8.36, U9.2, U10.2, U11.1, U11.4, U11.6, U11.9, U12.C5, U12.C8, U12.H3, U12.J3, U12.K11, U12.K12, U12.L5, U12.L6, U12.M8, U12.M11, U12.N8, U12.N12, U13.1, U13.2, U13.3, U13.4, U13.EPAD, U14.4, U14.EPAD, Y2.2, Y2.4
GND2: C43.2, C44.2, C45.2, C46.2, C47.2, C48.2, C49.2, C50.2, C51.2, C52.2, C53.2, C54.2, C55.2, C56.2, C57.2, C58.2, C59.2, C60.2, C61.2, C62.2, C63.2, D17.2, D19.C, J13.25, J14.GND, J14.GND2, J15.1, J16.1, J17.6, J17.GND1, J17.GND2, J17.GND3, J17.GND4, J17.GND5, J17.GND6, J18.2, R44.1, R46.1, R47.1, R48.1, R49.1, R52.1, R60.1, S3.1, S3.2, SHLD2.1, TP33.1, U15.1, U15.14, U15.23, U15.32, U15.34, U15.35, U15.36, U16.2, U17.2, U18.1, U18.4, U18.6, U18.9, U19.C5, U19.C8, U19.H3, U19.J3, U19.K11, U19.K12, U19.L5, U19.L6, U19.M8, U19.M11, U19.N8, U19.N12, U20.1, U20.2, U20.3, U20.4, U20.EPAD, U21.4, U21.EPAD, Y3.2, Y3.4
GND3: C64.2, C65.2, C66.2, C67.2, C68.2, C69.2, C70.2, C71.2, C72.2, C73.2, C74.2, C75.2, C76.2, C77.2, C78.2, C79.2, C80.2, C81.2, C82.2, C83.2, C84.2, D24.2, D26.C, J19.25, J20.GND, J20.GND2, J21.1, J22.1, J23.6, J23.GND1, J23.GND2, J23.GND3, J23.GND4, J23.GND5, J23.GND6, J24.2, R65.1, R67.1, R68.1, R69.1, R70.1, R73.1, R81.1, S4.1, S4.2, SHLD3.1, TP47.1, U22.1, U22.14, U22.23, U22.32, U22.34, U22.35, U22.36, U23.2, U24.2, U25.1, U25.4, U25.6, U25.9, U26.C5, U26.C8, U26.H3, U26.J3, U26.K11, U26.K12, U26.L5, U26.L6, U26.M8, U26.M11, U26.N8, U26.N12, U27.1, U27.2, U27.3, U27.4, U27.EPAD, U28.4, U28.EPAD, Y4.2, Y4.4
GND4: C85.2, C86.2, C87.2, C88.2, C89.2, C90.2, C91.2, C92.2, C93.2, C94.2, C95.2, C96.2, C97.2, C98.2, C99.2, C100.2, C101.2, C102.2, C103.2, C104.2, C105.2, D31.2, D33.C, J25.25, J26.GND, J26.GND2, J27.1, J28.1, J29.6, J29.GND1, J29.GND2, J29.GND3, J29.GND4, J29.GND5, J29.GND6, J30.2, R86.1, R88.1, R89.1, R90.1, R91.1, R94.1, R102.1, S5.1, S5.2, SHLD4.1, TP61.1, U29.1, U29.14, U29.23, U29.32, U29.34, U29.35, U29.36, U30.2, U31.2, U32.1, U32.4, U32.6, U32.9, U33.C5, U33.C8, U33.H3, U33.J3, U33.K11, U33.K12, U33.L5, U33.L6, U33.M8, U33.M11, U33.N8, U33.N12, U34.1, U34.2, U34.3, U34.4, U34.EPAD, U35.4, U35.EPAD, Y5.2, Y5.4
GND5: C106.2, C107.2, C108.2, C109.2, C110.2, C111.2, C112.2, C113.2, C114.2, C115.2, C116.2, C117.2, C118.2, C119.2, C120.2, C121.2, C122.2, C123.2, C124.2, C125.2, C126.2, D38.2, D40.C, J31.25, J32.GND, J32.GND2, J33.1, J34.1, J35.6, J35.GND1, J35.GND2, J35.GND3, J35.GND4, J35.GND5, J35.GND6, J36.2, R107.1, R109.1, R110.1, R111.1, R112.1, R115.1, R123.1, S6.1, S6.2, SHLD5.1, TP75.1, U36.1, U36.14, U36.23, U36.32, U36.34, U36.35, U36.36, U37.2, U38.2, U39.1, U39.4, U39.6, U39.9, U40.C5, U40.C8, U40.H3, U40.J3, U40.K11, U40.K12, U40.L5, U40.L6, U40.M8, U40.M11, U40.N8, U40.N12, U41.1, U41.2, U41.3, U41.4, U41.EPAD, U42.4, U42.EPAD, Y6.2, Y6.4
GND6: C127.2, C128.2, C129.2, C130.2, C131.2, C132.2, C133.2, C134.2, C135.2, C136.2, C137.2, C138.2, C139.2, C140.2, C141.2, C142.2, C143.2, C144.2, C145.2, C146.2, C147.2, D45.2, D47.C, J37.25, J38.GND, J38.GND2, J39.1, J40.1, J41.6, J41.GND1, J41.GND2, J41.GND3, J41.GND4, J41.GND5, J41.GND6, J42.2, R128.1, R130.1, R131.1, R132.1, R133.1, R136.1, R144.1, S7.1, S7.2, SHLD6.1, TP89.1, U43.1, U43.14, U43.23, U43.32, U43.34, U43.35, U43.36, U44.2, U45.2, U46.1, U46.4, U46.6, U46.9, U47.C5, U47.C8, U47.H3, U47.J3, U47.K11, U47.K12, U47.L5, U47.L6, U47.M8, U47.M11, U47.N8, U47.N12, U48.1, U48.2, U48.3, U48.4, U48.EPAD, U49.4, U49.EPAD, Y7.2, Y7.4
GND7: C148.2, C149.2, C150.2, C151.2, C152.2, C153.2, C154.2, C155.2, C156.2, C157.2, C158.2, C159.2, C160.2, C161.2, C162.2, C163.2, C164.2, C165.2, C166.2, C167.2, C168.2, D52.2, D54.C, J43.25, J44.GND, J44.GND2, J45.1, J46.1, J47.6, J47.GND1, J47.GND2, J47.GND3, J47.GND4, J47.GND5, J47.GND6, J48.2, R149.1, R151.1, R152.1, R153.1, R154.1, R157.1, R165.1, S8.1, S8.2, SHLD7.1, TP103.1, U50.1, U50.14, U50.23, U50.32, U50.34, U50.35, U50.36, U51.2, U52.2, U53.1, U53.4, U53.6, U53.9, U54.C5, U54.C8, U54.H3, U54.J3, U54.K11, U54.K12, U54.L5, U54.L6, U54.M8, U54.M11, U54.N8, U54.N12, U55.1, U55.2, U55.3, U55.4, U55.EPAD, U56.4, U56.EPAD, Y8.2, Y8.4
GND8: C169.2, C170.2, C171.2, C172.2, C173.2, C174.2, C175.2, C176.2, C177.2, C178.2, C179.2, C180.2, C181.2, C182.2, C183.2, C184.2, C185.2, C186.2, C187.2, C188.2, C189.2, D59.2, D61.C, J49.25, J50.GND, J50.GND2, J51.1, J52.1, J53.6, J53.GND1, J53.GND2, J53.GND3, J53.GND4, J53.GND5, J53.GND6, J54.2, R170.1, R172.1, R173.1, R174.1, R175.1, R178.1, R186.1, S9.1, S9.2, SHLD8.1, TP117.1, U57.1, U57.14, U57.23, U57.32, U57.34, U57.35, U57.36, U58.2, U59.2, U60.1, U60.4, U60.6, U60.9, U61.C5, U61.C8, U61.H3, U61.J3, U61.K11, U61.K12, U61.L5, U61.L6, U61.M8, U61.M11, U61.N8, U61.N12, U62.1, U62.2, U62.3, U62.4, U62.EPAD, U63.4, U63.EPAD, Y9.2, Y9.4
GND9: C190.2, C191.2, C192.2, C193.2, C194.2, C195.2, C196.2, C197.2, C198.2, C199.2, C200.2, C201.2, C202.2, C203.2, C204.2, C205.2, C206.2, C207.2, C208.2, C209.2, C210.2, D66.2, D68.C, J55.25, J56.GND, J56.GND2, J57.1, J58.1, J59.6, J59.GND1, J59.GND2, J59.GND3, J59.GND4, J59.GND5, J59.GND6, J60.2, R191.1, R193.1, R194.1, R195.1, R196.1, R199.1, R207.1, S10.1, S10.2, SHLD9.1, TP131.1, U64.1, U64.14, U64.23, U64.32, U64.34, U64.35, U64.36, U65.2, U66.2, U67.1, U67.4, U67.6, U67.9, U68.C5, U68.C8, U68.H3, U68.J3, U68.K11, U68.K12, U68.L5, U68.L6, U68.M8, U68.M11, U68.N8, U68.N12, U69.1, U69.2, U69.3, U69.4, U69.EPAD, U70.4, U70.EPAD, Y10.2, Y10.4
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
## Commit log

2022-06-13 Add MGM240P library file
2022-06-13 Add initial schematic and layout
2022-06-15 Add PROD_ID to MGM240P
2022-06-15 Schematic and board updates
    Disconnect RTS and CTS pins
    Add status LED
    Complete more of the routing and component placement
2022-06-15 Finalize initial schematic and board
    Clean up schematic and finalize nets
    Finish routing board (needs improved GND continuity
2022-06-15 Add polish
    Improve GND continuity
    Fix and approve DRC errors
    Add SFE flame and OSHW logo to top silk
    Add pin and jumper labels to bottom silk
2022-06-15 Update voltage regulator
2022-06-16 Design review updates
    Add reset button
    Add power LED
    Pour USB shield on bottom too
    Increase VUSB trace to 20mil
    Add silk labels for LEDs
    Add version number to copper
2022-06-16 Design review updates
    Chang USB connector to 2-layer version
    Fix gague typo in schematic
    Remove UART flow control nets from J-Link
    Spread out J-Link caps in schematic
    Remove right angles from VDDJ trace and straighten out
    Fix acid trap
2022-06-17 Design review updates
    Change to 4-layer board for better EMC and routing
    Remove excessive GND vias now that it's 4 layers
    Add label to reset button in silk
    Add 10uF cap for SD card
    Change net names to represent MGM240P port names rather than Arduino names
    Connect uSD CS pin to PA07
2022-06-17 Update MGM240P with cutout polygons on inner layers
2022-06-17 Create library part for J-Link 6 Pin Adapter
2022-06-17 Update silk width of MGM240P
    Board ULP was giving warning
2022-06-17 Design review and checklist updates
    Swap J-Link test points for new part
    Change size of STAT silk and add pin number
    Adjust fuel gauge cap position
    Adjust board name silk positions
    Add ordering instructions (4 layer board)
    Improve GND continuity
2022-06-17 Add name and value to J-Link connector footprint
2022-06-17 Design review updates
    Change USB-C connector to 4-layer version
    Add units to measures
    Update J-Link footprint
2022-06-20 Minor board updates
    Shift MEAS jumper to not interfere with R4
    Add GND via under J-Link
    Add SHLD via to fix air wire between layers
2022-07-11 Add new debugger part library files
2022-07-11 Remove J-Link 6-pin adapter part
    Not going to use it
2022-07-11 Update board with new debugger chip
    Middle region of board had to be completely rerouted
2022-07-11 Finish debugger power circuitry
2022-07-12 Change serial flash chip to different package
    Previous package is NRND
2022-07-12 Serial flash and routing updates
    Update serial flash chip and routing for it
    Change routing of debugger chip to not require 3.5 mil traces
2022-07-13 Add documents
2022-07-13 Minor routing improvements
    Route TX through unused pin on debugger chip
    Improve GND continuity
2022-07-14 Add alternate functions to MGM240P and EFM32 symbols
2022-07-14 Update board
    Update EFM32 and MGM240P symbols
    Remove JTAG labels from net names
2022-07-14 Fix merge issue
    Forgot to pull changes from home, whoops...
2022-07-14 Checklist and design review updates
    Add warning about holding GPIO pins high while chip not powered
    Change status LED resistor value
    Fix EFM32 name and value not appearing in board
    Fix U2 part number missing in schematic
    Move USB connector to left side of schematic
    Move C7 to fit U3D part number in schematic
2022-07-14 Design review updates
    Make EFM32 symbol D wider to not have pin names interleaved
    Tweak location of test points in schematic to match relative locations on board
    Route pads from centers better
    Adjust CC resistor positions
    Widen V_USB trace under USB connector and add more vias
    Change V_USB trace in power layer to wider polygon
2022-07-14 Design review updates
    Fix measurements on right side of board
    Rename VDDJ net from VDD to VDDJ
    Add "FREE" to C7 silk
    Replace J Link power control circuitry with a NC jumper
    Move reset button next to battery connector
    Improve continuity of 3V3 pour
2022-07-15 Update new parts
    Add PROD_ID
    Add descriptions
2022-07-15 Add keepout region to new parts
2022-07-18 Design review updates
    Shift debug circuitry downwards
    Add 48MHz crystal
    Fix V_BATT and V_USB being flipped on Thing Plus pinout
    Add pullup resistors for debugger I2C and CS lines
    Add filter caps for debugger chip
    Change C7 to X7R 0603 for better derating performance
2022-07-18 Design review updates
    Fix V_BATT and V_USB label locations
    Move VDDJ label to not interfere with GND label
    Move crystal away from C9
2022-07-18 Add PROD_ID to crystal
2022-07-19 Change debugger power circuitry
    Remove VDDJ jumper
    Remove VDDJ net and replace with 3V3
    Add DBG_WAKE net and circuitry, which controls sleep state of debugger chip
2022-07-19 Design review updates
    Remove VDDJ label from silk
    Add jumper to debugger power control circuit for USB battery applications
2022-07-19 Add proto production files
2022-08-01 Testing fixes
    Update version number to v02
    Mirror MX8035 footprint (whoops...)
    Swap R15 for 2k2 (turns out VREGO is 3V3, not 5V)
    Add trace to 3V3 pour to connect between V_USB and N$24
2022-08-01 Design review updates
    Adjust DBG_SCK trace
    Remove extra GND trace of C6
2022-08-02 Flip DBG TX and RX
2022-08-02 Swap PA04 and PA07
2022-08-02 Update proto production files for v02
2022-09-07 Design review updates
    Add GND vias along antenna cutout edge
    Add extra GND vias near MGM240P GND pads
    Add pullup resistor to SD card CS pin
    Add extra GND vias between I2C and SPI traces on bottom
    Widen DECOUPLE trace
    Add series resistors to MGM240P's RX inputs to prevent contention between debugger, Mini Simplicity connector, and Thing Plus RX pin
2022-09-07 Design review updates
    Change voltage regulator to specify maximum input voltage only
    Add Segger logo
    Move traces away from jumpers to prevent accidental cutting
2022-09-07 Fix air wire
2022-09-07 Update revision number to v10
2022-09-08 Design review updates
    Add "ENIG Finish" to ordering instructions
    Add jumpers for rerouting reset line to A0 pin
2022-09-09 Add Silicon Labs logo
2022-09-09 Add text to RST and D3_ISO jumpers
2022-09-09 Design review updates
    Move RST jumper to align with D3_ISO jumper
    Add silk label to CHG_I jumper
    Move R20 left 25 mils
2022-09-09 Design review updates
    Nudge RX/PA06 away from N$25
    Add text to schematic explaining escape routing connections
    Change RST jumper to "JP1" to make people read the docs
    Remove "Thing Plus" from bottom silkscreen
2022-09-09 Design review changes
    Fix acid traps
    Change JP1 silk
2022-09-09 Add v10 production files
2022-09-09 Remove extraneous silk
2022-09-09 Update v10 production files
2022-09-20 Add MGM240P Datasheet
2022-10-04 Update README.md
    Initial commit of README.md with product links.
2022-10-06 Change R3 from 10k to 100k
    Improves low power consumption
2022-10-31 Update README.md
    Adding product photo to README.md
2023-03-01 Update README.md
    Updating readme with Hookup Guide link.
2023-03-02 Update README.md
    Fixing content folders list.
2023-03-29 Remove library files
    Parts are in SFE Eagle library, update parts in design
2023-06-20 Update README.md
    Updating product image link.
